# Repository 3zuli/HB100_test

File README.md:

# HB100_test
A quick test of the cheap HB100 doppler radar module. Can be bought on ebay for ~$5. The module works by 
outputting a square waveform from its IF pin at frequency of the detected Doppler shift. However this signal is only
a copule microvolts peak-to-peak, so we need a pre-amplifier to boost the signal to 5V logic levels.

Datasheet of the module: https://www.openimpulse.com/blog/wp-content/uploads/wpsc/downloadables/HB100_Microwave_Sensor_Application_Note.pdf

HW requirements:
* Arduino Uno / Nano / Pro mini
* HB100 module + pre-amp board
* 1602 or similar LCD 

SW requirements:
* FreqMeasure library http://www.pjrc.com/teensy/td_libs_FreqMeasure.html (located in /HB100_LCD_Output/FreqMeasure folder)

The "design" folder contains design files of the pre-amp board for Eagle. The circuit was taken from the above
datasheet, I just designed the PCB for it. Ready-made preamp boards are available from here:
http://www.limpkin.fr/index.php?post/2013/08/09/Making-the-electronics-for-a-%247-USD-doppler-motion-sensor

The "HB100_LCD_output" folder contains the Arduino source code. The code is just the slightly modified LCD example from FreqMeasure. In the loop, we take 30 frequency measurements, then get the average value and display it on the LCD. This was tested on an Arduino Nano and should work as well on Uno and Pro Mini. For other boards, see the FreqMeasure documentation below.

Additional info:
* http://jpnelson.com/post/37623468093/microwave-motion-sensors-for-fun-and-profit-hb100
* http://forum.arduino.cc/index.php?topic=61989.0
* http://www.limpkin.fr/index.php?post/2013/08/09/Making-the-electronics-for-a-%247-USD-doppler-motion-sensor

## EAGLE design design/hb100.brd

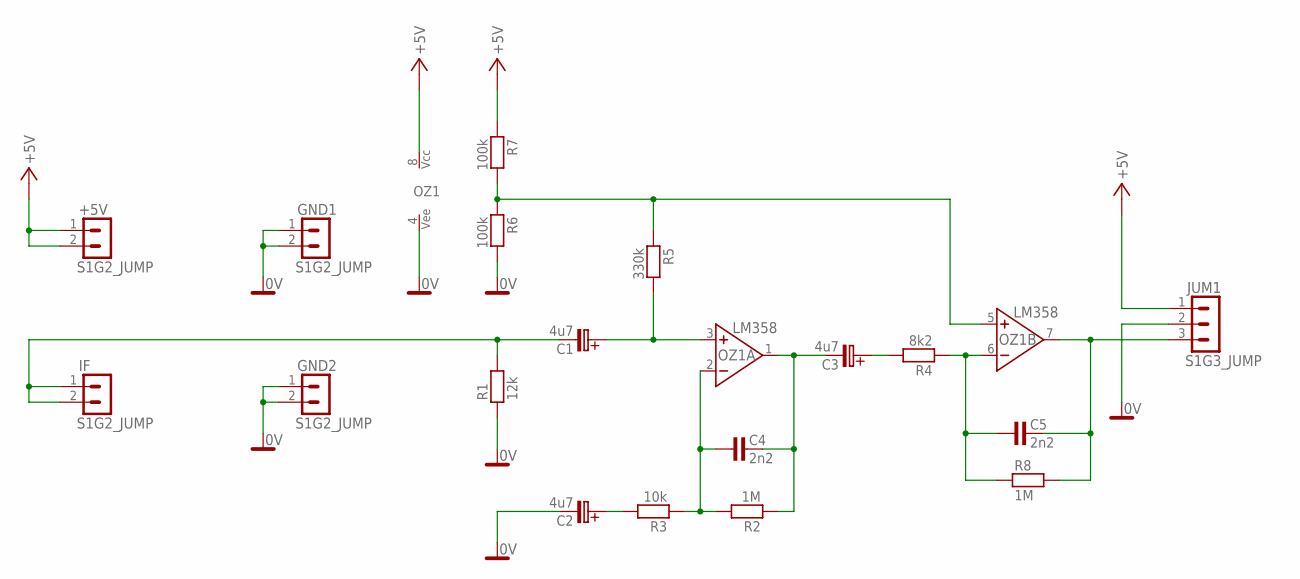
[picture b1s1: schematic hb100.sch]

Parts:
+5V: S1G2_JUMP; S1G2_JUM
C1, C2, C3: 4u7; C-EL_3,5
C4, C5: 2n2; C-5
GND1, GND2: S1G2_JUMP; S1G2_JUM
IF: S1G2_JUMP; S1G2_JUM
JUM1: S1G3_JUMP; S1G3_JUM
OZ1: LM358; DIL8
R1: 12k; R-7,5
R2, R8: 1M; R-7,5
R3: 10k; R-7,5
R4: 8k2; R-7,5
R5: 330k; R-7,5
R6, R7: 100k; R-7,5

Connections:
0V: C2.C- (C_EL-), GND1.1, GND1.2, GND2.1, GND2.2, JUM1.2, OZ1.4 (VEE), R1.1, R6.2
+5V: +5V.1, +5V.2, JUM1.1, OZ1.8 (VCC), R7.1
unnamed: C1.C- (C_EL-), IF.1, IF.2, R1.2
unnamed: C1.C+ (C_EL+), OZ1.3 (NEIN+), R5.2
unnamed: C3.C+ (C_EL+), R4.2
unnamed: OZ1.5 (NEIN+), R5.1, R6.1, R7.2
unnamed: C3.C- (C_EL-), C4.2, OZ1.1 (VYSTUP), R2.1
unnamed: C5.1, OZ1.6 (IN-), R4.1, R8.1
unnamed: C2.C+ (C_EL+), R3.2
unnamed: C4.1, OZ1.2 (IN-), R2.2, R3.1
unnamed: C5.2, JUM1.3, OZ1.7 (VYSTUP), R8.2

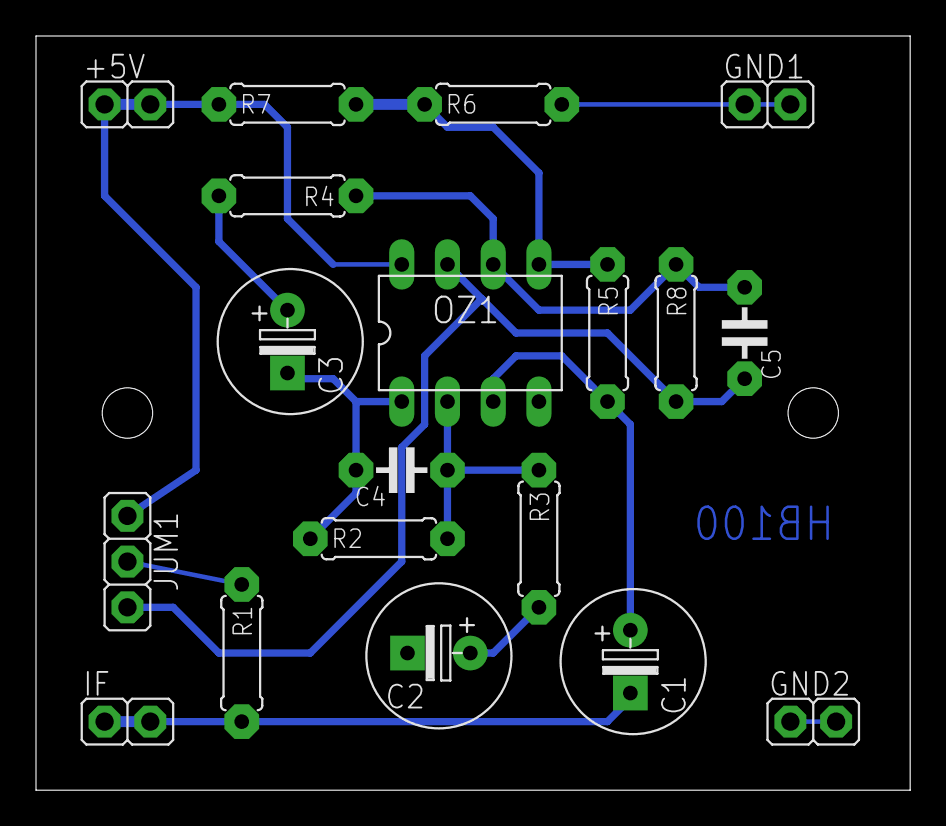
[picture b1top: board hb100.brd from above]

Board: 2 copper layers, 48.6 x 41.9 mm, 19 parts (0 on the bottom side), 11 nets.

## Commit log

2015-04-05 :confetti_ball: Added .gitattributes & .gitignore files
2015-11-27 Add rendered circuit diagram
2016-04-18 Use the included FreqMeasure library

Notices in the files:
parts and their libraries:
Copyright (C) PaJa 2011
Copyright (C) PaJa 2001-2011
